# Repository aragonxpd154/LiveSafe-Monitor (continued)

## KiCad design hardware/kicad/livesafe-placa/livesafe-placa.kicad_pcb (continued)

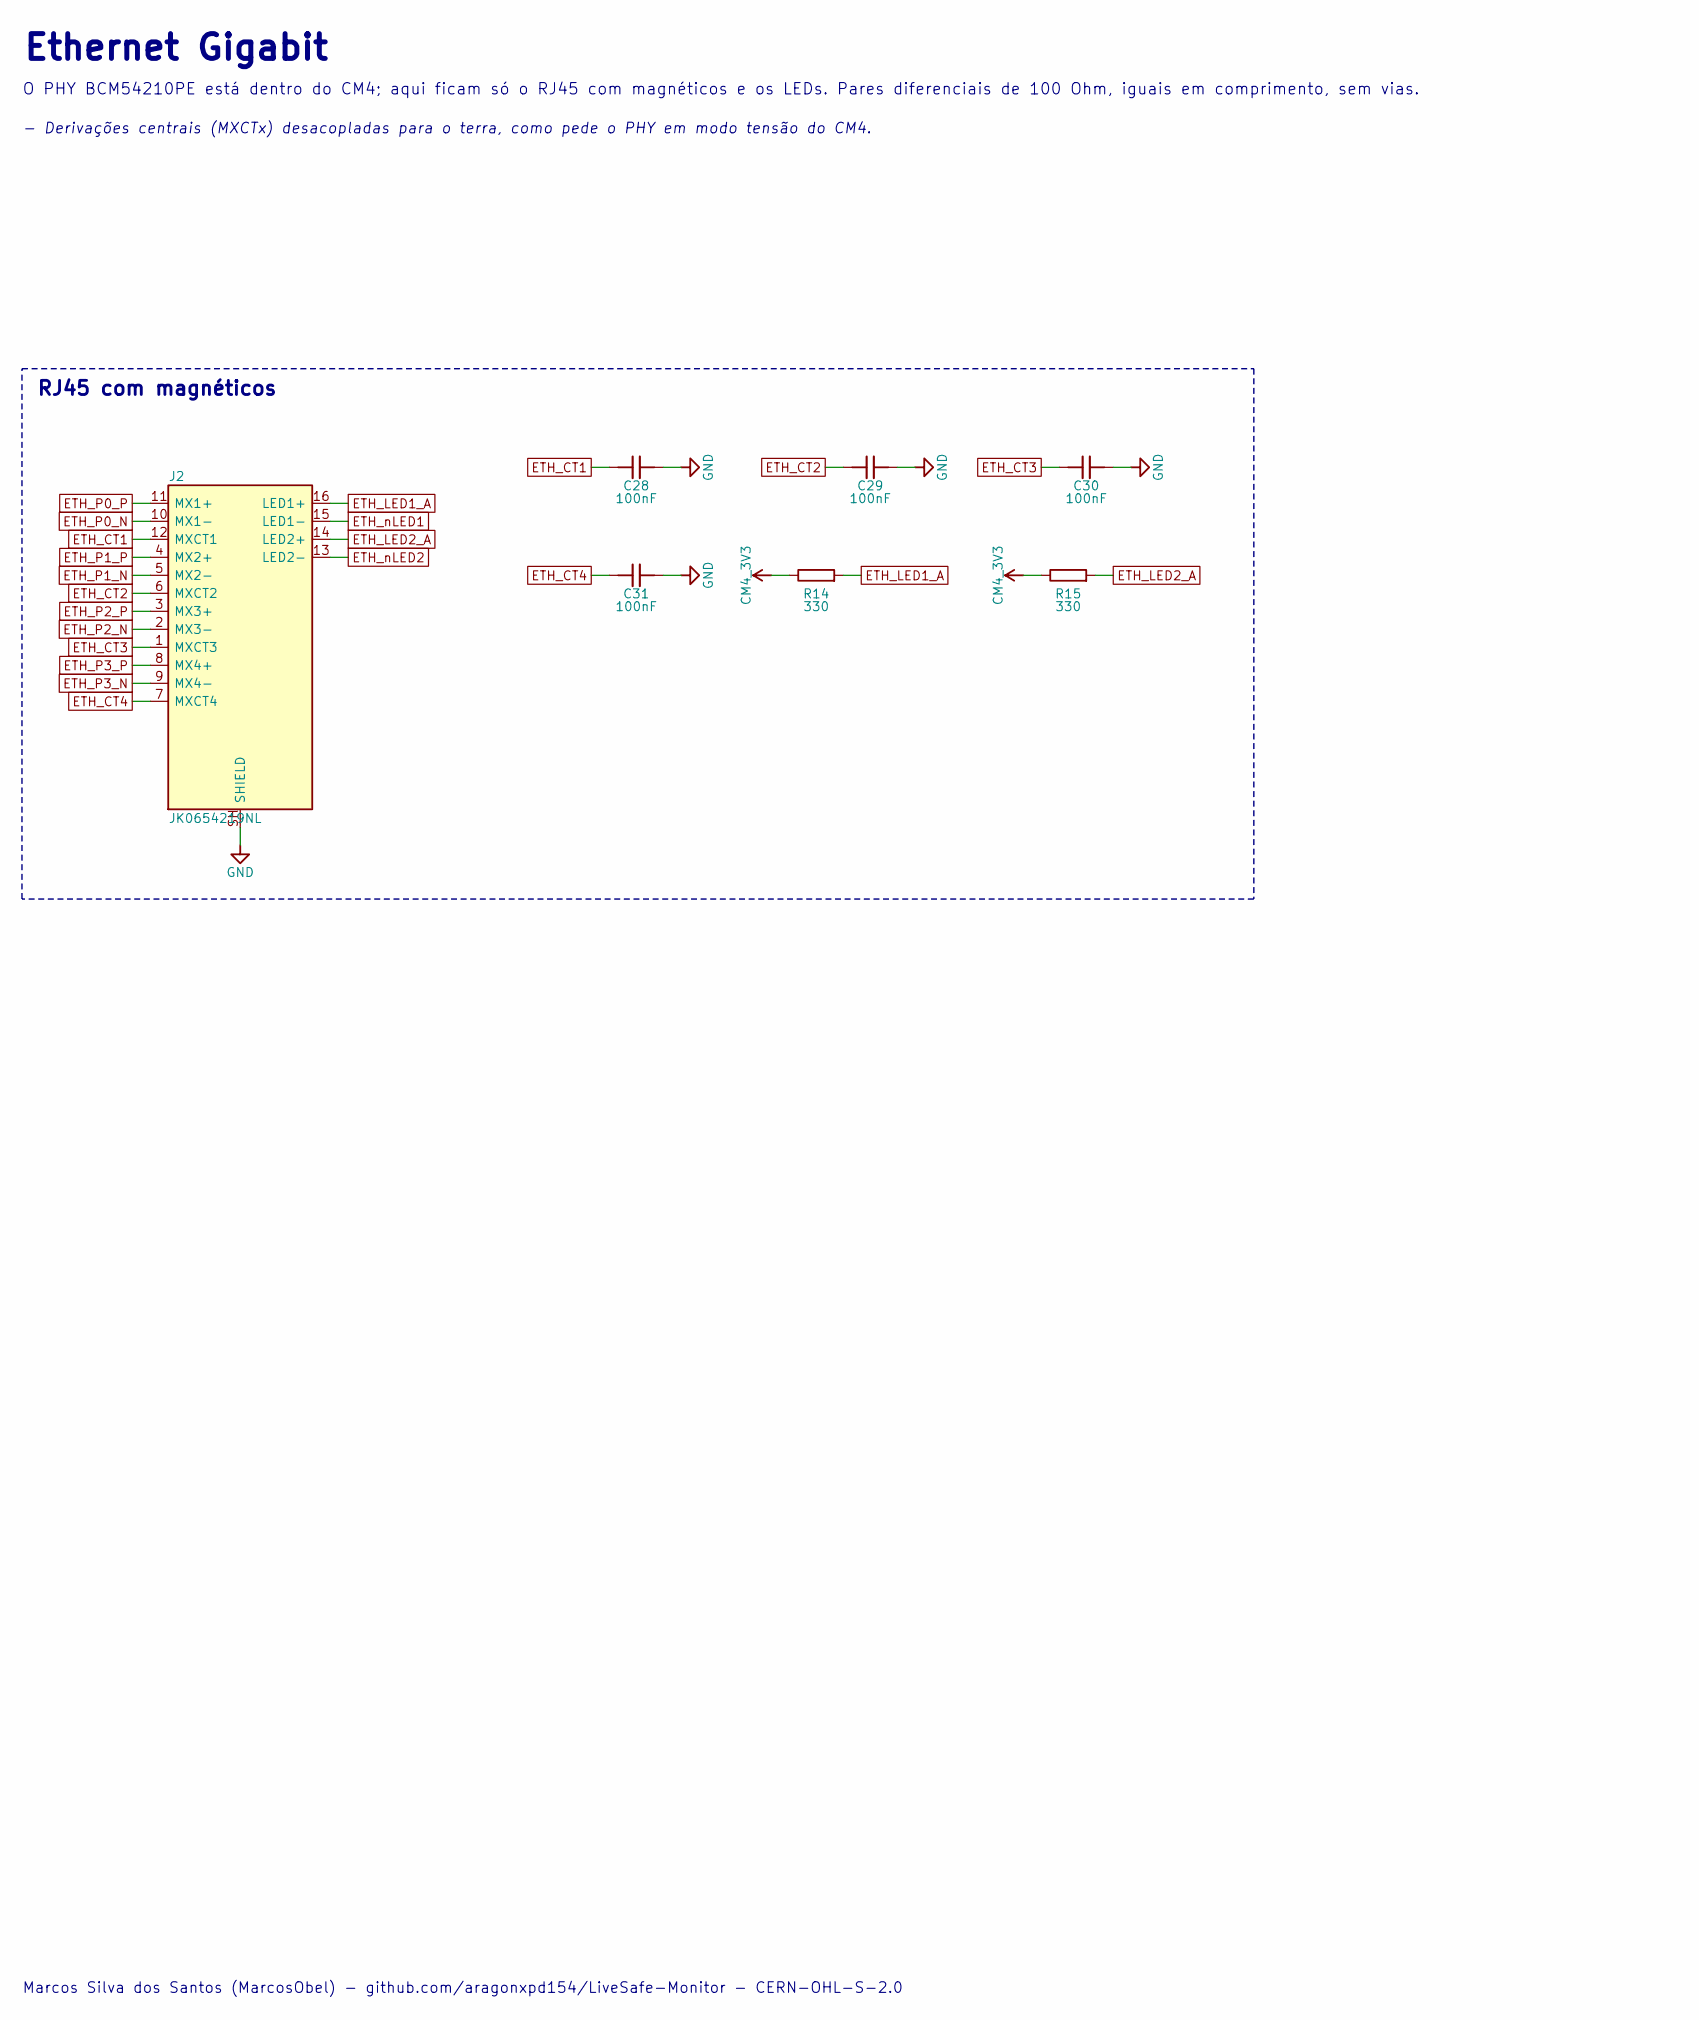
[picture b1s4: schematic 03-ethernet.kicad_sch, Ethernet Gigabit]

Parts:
C28, C29, C30, C31: 100nF; C_0402_1005Metric; MPN CL05B104KO5NNNC; LCSC C1525
J2: JK0654219NL; RJ45_Pulse_JK0654219NL_Horizontal; MPN JK0654219NL
R14, R15: 330; R_0402_1005Metric; MPN 0402WGF3300TCE; LCSC C25104

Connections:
CM4_3V3: R14.1, R15.1; also elsewhere on the board
ETH_CT1: C28.1, J2.12 (MXCT1)
ETH_CT2: C29.1, J2.6 (MXCT2)
ETH_CT3: C30.1, J2.1 (MXCT3)
ETH_CT4: C31.1, J2.7 (MXCT4)
ETH_LED1_A: J2.16 (LED1+), R14.2
ETH_LED2_A: J2.14 (LED2+), R15.2
ETH_P0_N: J2.10 (MX1-); also elsewhere on the board
ETH_P0_P: J2.11 (MX1+); also elsewhere on the board
ETH_P1_N: J2.5 (MX2-); also elsewhere on the board
ETH_P1_P: J2.4 (MX2+); also elsewhere on the board
ETH_P2_N: J2.2 (MX3-); also elsewhere on the board
ETH_P2_P: J2.3 (MX3+); also elsewhere on the board
ETH_P3_N: J2.9 (MX4-); also elsewhere on the board
ETH_P3_P: J2.8 (MX4+); also elsewhere on the board
ETH_nLED1: J2.15 (LED1-); also elsewhere on the board
ETH_nLED2: J2.13 (LED2-); also elsewhere on the board
GND: C28.2, C29.2, C30.2, C31.2, J2.SH (SHIELD); also elsewhere on the board

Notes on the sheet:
RJ45 com magnéticos
Ethernet Gigabit
O PHY BCM54210PE está dentro do CM4; aqui ficam só o RJ45 com magnéticos e os LEDs. Pares diferenciais de 100 Ohm, iguais em comprimento, sem vias.
- Derivações centrais (MXCTx) desacopladas para o terra, como pede o PHY em modo tensão do CM4.
Marcos Silva dos Santos (MarcosObel) - github.com/aragonxpd154/LiveSafe-Monitor - CERN-OHL-S-2.0

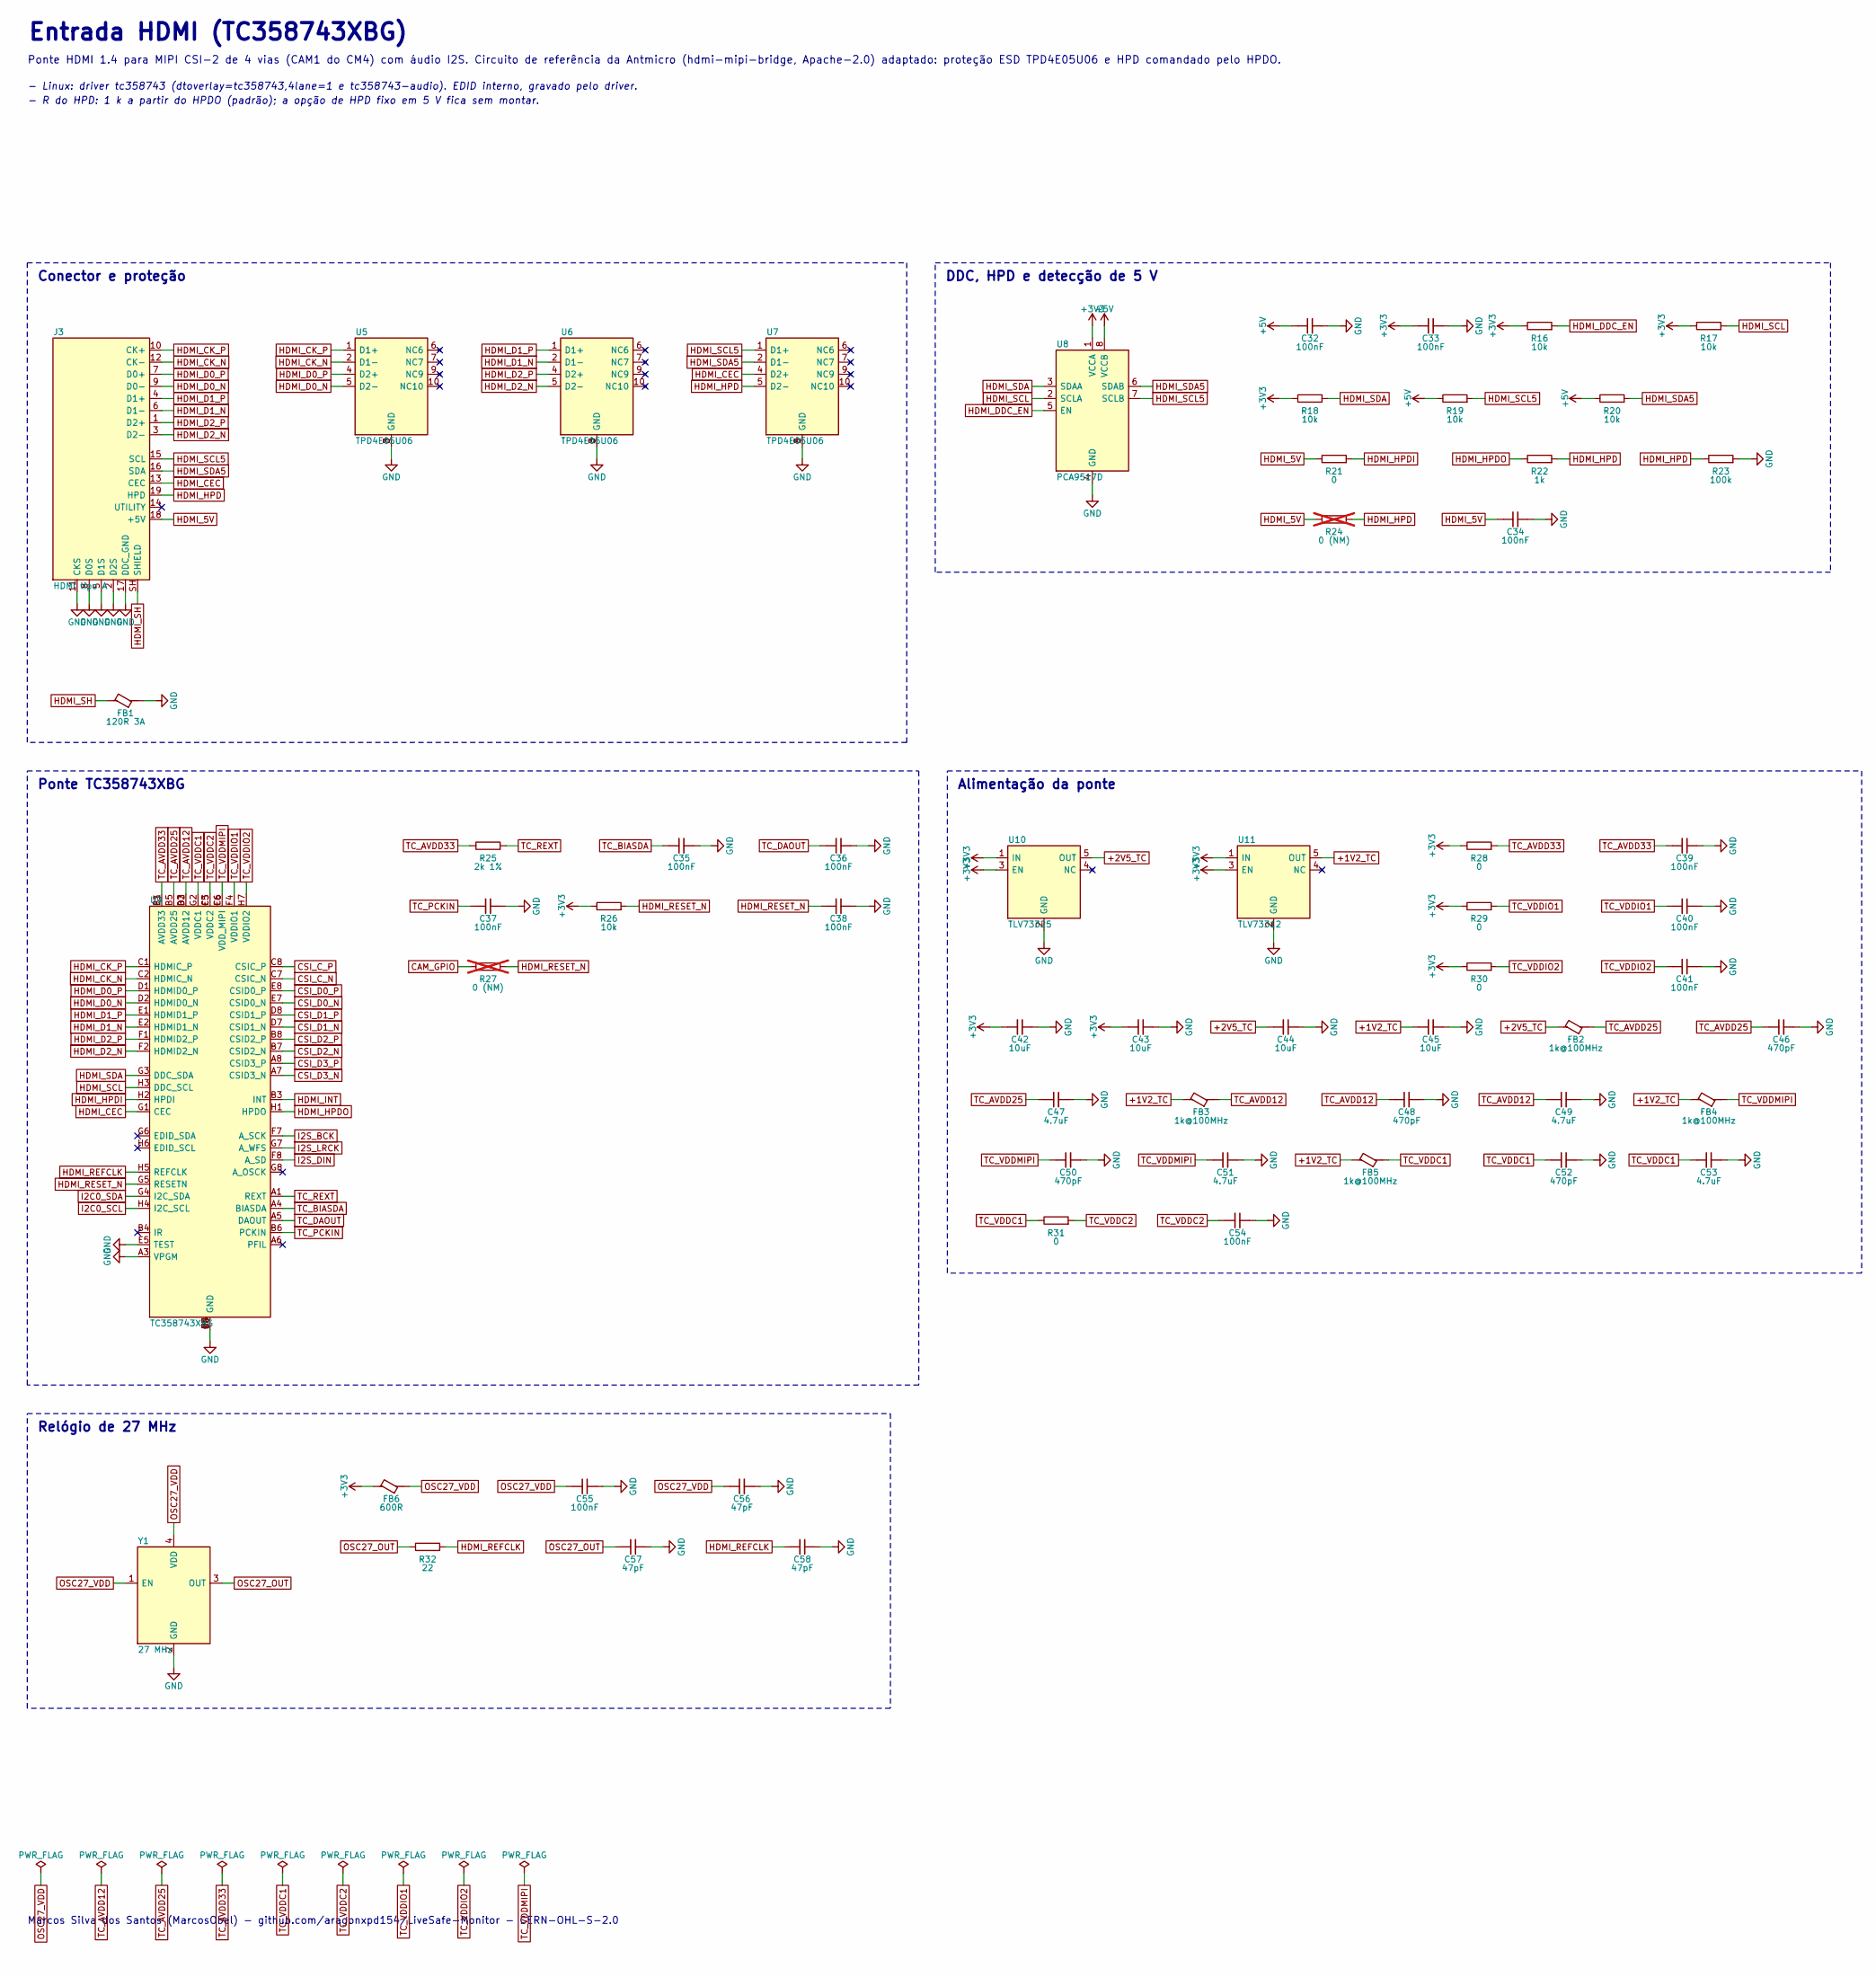
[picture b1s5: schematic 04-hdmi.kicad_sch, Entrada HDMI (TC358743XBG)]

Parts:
C32, C33, C34, C35, C36, C37, C38, C39, C40, C41, C54, C55: 100nF; C_0402_1005Metric; MPN CL05B104KO5NNNC; LCSC C1525
C42, C43, C44, C45: 10uF; C_0603_1608Metric; MPN CL10A106KP8NNNC; LCSC C19702
C46, C48, C50, C52: 470pF; C_0402_1005Metric; MPN CL05B471KB5NNNC; LCSC C26412
C47, C49, C51, C53: 4.7uF; C_0603_1608Metric; MPN CL10A475KO8NNNC; LCSC C19666
C56, C57, C58: 47pF; C_0402_1005Metric; MPN CL05C470JB5NNNC; LCSC C84706
FB1: 120R 3A; L_0603_1608Metric; MPN BLM18SG121TN1D; LCSC C113030
FB2, FB3, FB4, FB5: 1k@100MHz; L_0805_2012Metric; MPN BLM21AG102SN1D; LCSC C85835
FB6: 600R; L_0603_1608Metric; MPN BLM18AG601SN1D; LCSC C19330
J3: HDMI tipo A; HDMI_A_Molex_208658-1001_Horizontal; MPN 2086581001; LCSC C916313
R16, R17, R18, R19, R20, R26: 10k; R_0402_1005Metric; MPN 0402WGF1002TCE; LCSC C25744
R21, R28, R29, R30, R31: 0; R_0603_1608Metric; MPN 0603WAF0000T5E; LCSC C21189
R22: 1k; R_0402_1005Metric; MPN 0402WGF1001TCE; LCSC C11702
R23: 100k; R_0402_1005Metric; MPN 0402WGF1003TCE; LCSC C25741
R24: 0 (NM); R_0603_1608Metric; MPN 0603WAF0000T5E; LCSC C21189; not fitted
R25: 2k 1%; R_0402_1005Metric; MPN 0402WGF2001TCE; LCSC C4109
R27: 0 (NM); R_0402_1005Metric; MPN 0402WGF0000TCE; LCSC C17168; not fitted
R32: 22; R_0402_1005Metric; MPN 0402WGF220JTCE; LCSC C25092
U5, U6, U7: TPD4E05U06; USON-10_2.5x1.0mm_P0.5mm; MPN TPD4E05U06DQAR; LCSC C138714
U8: PCA9517D; SOIC-8_3.9x4.9mm_P1.27mm; MPN PCA9517D,118; LCSC C2652395
U9: TC358743XBG; Toshiba_P-TFBGA64-0606-0.65; MPN TC358743XBG
U10: TLV73325; SOT-23-5; MPN TLV73325PDBVR; LCSC C882825
U11: TLV73312; SOT-23-5; MPN TLV73312PDBVR; LCSC C473364
Y1: 27 MHz; Oscillator_SMD_Abracon_ASE-4Pin_3.2x2.5mm; MPN ASE-27.000MHZ-LC-T; LCSC C1988528

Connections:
+1V2_TC: C45.1, FB3.1, FB4.1, FB5.1, U11.5 (OUT)
+2V5_TC: C44.1, FB2.1, U10.5 (OUT)
+3V3: C33.1, C42.1, C43.1, FB6.1, R16.1, R17.1, R18.1, R26.1, R28.1, R29.1, R30.1, U8.1 (VCCA), U10.1 (IN), U10.3 (EN), U11.1 (IN), U11.3 (EN); also elsewhere on the board
+5V: C32.1, R19.1, R20.1, U8.8 (VCCB); also elsewhere on the board
CAM_GPIO: R27.1; also elsewhere on the board
CSI_C_N: U9.C7 (CSIC_N); also elsewhere on the board
CSI_C_P: U9.C8 (CSIC_P); also elsewhere on the board
CSI_D0_N: U9.E7 (CSID0_N); also elsewhere on the board
CSI_D0_P: U9.E8 (CSID0_P); also elsewhere on the board
CSI_D1_N: U9.D7 (CSID1_N); also elsewhere on the board
CSI_D1_P: U9.D8 (CSID1_P); also elsewhere on the board
CSI_D2_N: U9.B7 (CSID2_N); also elsewhere on the board
CSI_D2_P: U9.B8 (CSID2_P); also elsewhere on the board
CSI_D3_N: U9.A7 (CSID3_N); also elsewhere on the board
CSI_D3_P: U9.A8 (CSID3_P); also elsewhere on the board
GND: C32.2, C33.2, C34.2, C35.2, C36.2, C37.2, C38.2, C39.2, C40.2, C41.2, C42.2, C43.2, C44.2, C45.2, C46.2, C47.2, C48.2, C49.2, C50.2, C51.2, C52.2, C53.2, C54.2, C55.2, C56.2, C57.2, C58.2, FB1.2, J3.2 (D2S), J3.5 (D1S), J3.8 (D0S), J3.11 (CKS), J3.17 (DDC_GND), R23.2, U5.3 (GND), U5.8 (GND), U6.3 (GND), U6.8 (GND), U7.3 (GND), U7.8 (GND), U8.4 (GND), U9.A2 (GND), U9.A3 (VPGM), U9.C4 (GND), U9.C5 (GND), U9.D4 (GND), U9.D5 (GND), U9.D6 (GND), U9.E3 (GND), U9.E4 (GND), U9.E5 (TEST), U9.E6 (GND), U9.H8 (GND), U10.2 (GND), U11.2 (GND), Y1.2 (GND); also elsewhere on the board
HDMI_5V: C34.1, J3.18 (+5V), R21.1, R24.1
HDMI_CEC: J3.13 (CEC), U7.4 (D2+), U9.G1 (CEC)
HDMI_CK_N: J3.12 (CK-), U5.2 (D1-), U9.C2 (HDMIC_N)
HDMI_CK_P: J3.10 (CK+), U5.1 (D1+), U9.C1 (HDMIC_P)
HDMI_D0_N: J3.9 (D0-), U5.5 (D2-), U9.D2 (HDMID0_N)
HDMI_D0_P: J3.7 (D0+), U5.4 (D2+), U9.D1 (HDMID0_P)
HDMI_D1_N: J3.6 (D1-), U6.2 (D1-), U9.E2 (HDMID1_N)
HDMI_D1_P: J3.4 (D1+), U6.1 (D1+), U9.E1 (HDMID1_P)
HDMI_D2_N: J3.3 (D2-), U6.5 (D2-), U9.F2 (HDMID2_N)
HDMI_D2_P: J3.1 (D2+), U6.4 (D2+), U9.F1 (HDMID2_P)
HDMI_DDC_EN: R16.2, U8.5 (EN)
HDMI_HPD: J3.19 (HPD), R22.2, R23.1, R24.2, U7.5 (D2-)
HDMI_HPDI: R21.2, U9.H2 (HPDI)
HDMI_HPDO: R22.1, U9.H1 (HPDO)
HDMI_INT: U9.B3 (INT); also elsewhere on the board
HDMI_REFCLK: C58.1, R32.2, U9.H5 (REFCLK)
HDMI_RESET_N: C38.1, R26.2, R27.2, U9.G5 (RESETN)
HDMI_SCL: R17.2, U8.2 (SCLA), U9.H3 (DDC_SCL)
HDMI_SCL5: J3.15 (SCL), R19.2, U7.1 (D1+), U8.7 (SCLB)
HDMI_SDA: R18.2, U8.3 (SDAA), U9.G3 (DDC_SDA)
HDMI_SDA5: J3.16 (SDA), R20.2, U7.2 (D1-), U8.6 (SDAB)
HDMI_SH: FB1.1, J3.SH (SHIELD)
I2C0_SCL: U9.H4 (I2C_SCL); also elsewhere on the board
I2C0_SDA: U9.G4 (I2C_SDA); also elsewhere on the board
I2S_BCK: U9.F7 (A_SCK); also elsewhere on the board
I2S_DIN: U9.F8 (A_SD); also elsewhere on the board
I2S_LRCK: U9.G7 (A_WFS); also elsewhere on the board
OSC27_OUT: C57.1, R32.1, Y1.3 (OUT)
OSC27_VDD: C55.1, C56.1, FB6.2, Y1.1 (EN), Y1.4 (VDD)
TC_AVDD12: C48.1, C49.1, FB3.2, U9.B2 (AVDD12), U9.D3 (AVDD12)
TC_AVDD25: C46.1, C47.1, FB2.2, U9.B5 (AVDD25)
TC_AVDD33: C39.1, R25.1, R28.2, U9.B1 (AVDD33), U9.F3 (AVDD33)
TC_BIASDA: C35.1, U9.A4 (BIASDA)
TC_DAOUT: C36.1, U9.A5 (DAOUT)
TC_PCKIN: C37.1, U9.B6 (PCKIN)
TC_REXT: R25.2, U9.A1 (REXT)
TC_VDDC1: C52.1, C53.1, FB5.2, R31.1, U9.G2 (VDDC1)
TC_VDDC2: C54.1, R31.2, U9.C3 (VDDC2), U9.F5 (VDDC2)
TC_VDDIO1: C40.1, R29.2, U9.F4 (VDDIO1)
TC_VDDIO2: C41.1, R30.2, U9.H7 (VDDIO2)
TC_VDDMIPI: C50.1, C51.1, FB4.2, U9.C6 (VDD_MIPI), U9.F6 (VDD_MIPI)

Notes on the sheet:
Conector e proteção
DDC, HPD e detecção de 5 V
Ponte TC358743XBG
Alimentação da ponte
Relógio de 27 MHz
Entrada HDMI (TC358743XBG)
Ponte HDMI 1.4 para MIPI CSI-2 de 4 vias (CAM1 do CM4) com áudio I2S. Circuito de referência da Antmicro (hdmi-mipi-bridge, Apache-2.0) adaptado: proteção ESD TPD4E05U06 e HPD comandado pelo HPDO.
- Linux: driver tc358743 (dtoverlay=tc358743,4lane=1 e tc358743-audio). EDID interno, gravado pelo driver.
- R do HPD: 1 k a partir do HPDO (padrão); a opção de HPD fixo em 5 V fica sem montar.
Marcos Silva dos Santos (MarcosObel) - github.com/aragonxpd154/LiveSafe-Monitor - CERN-OHL-S-2.0

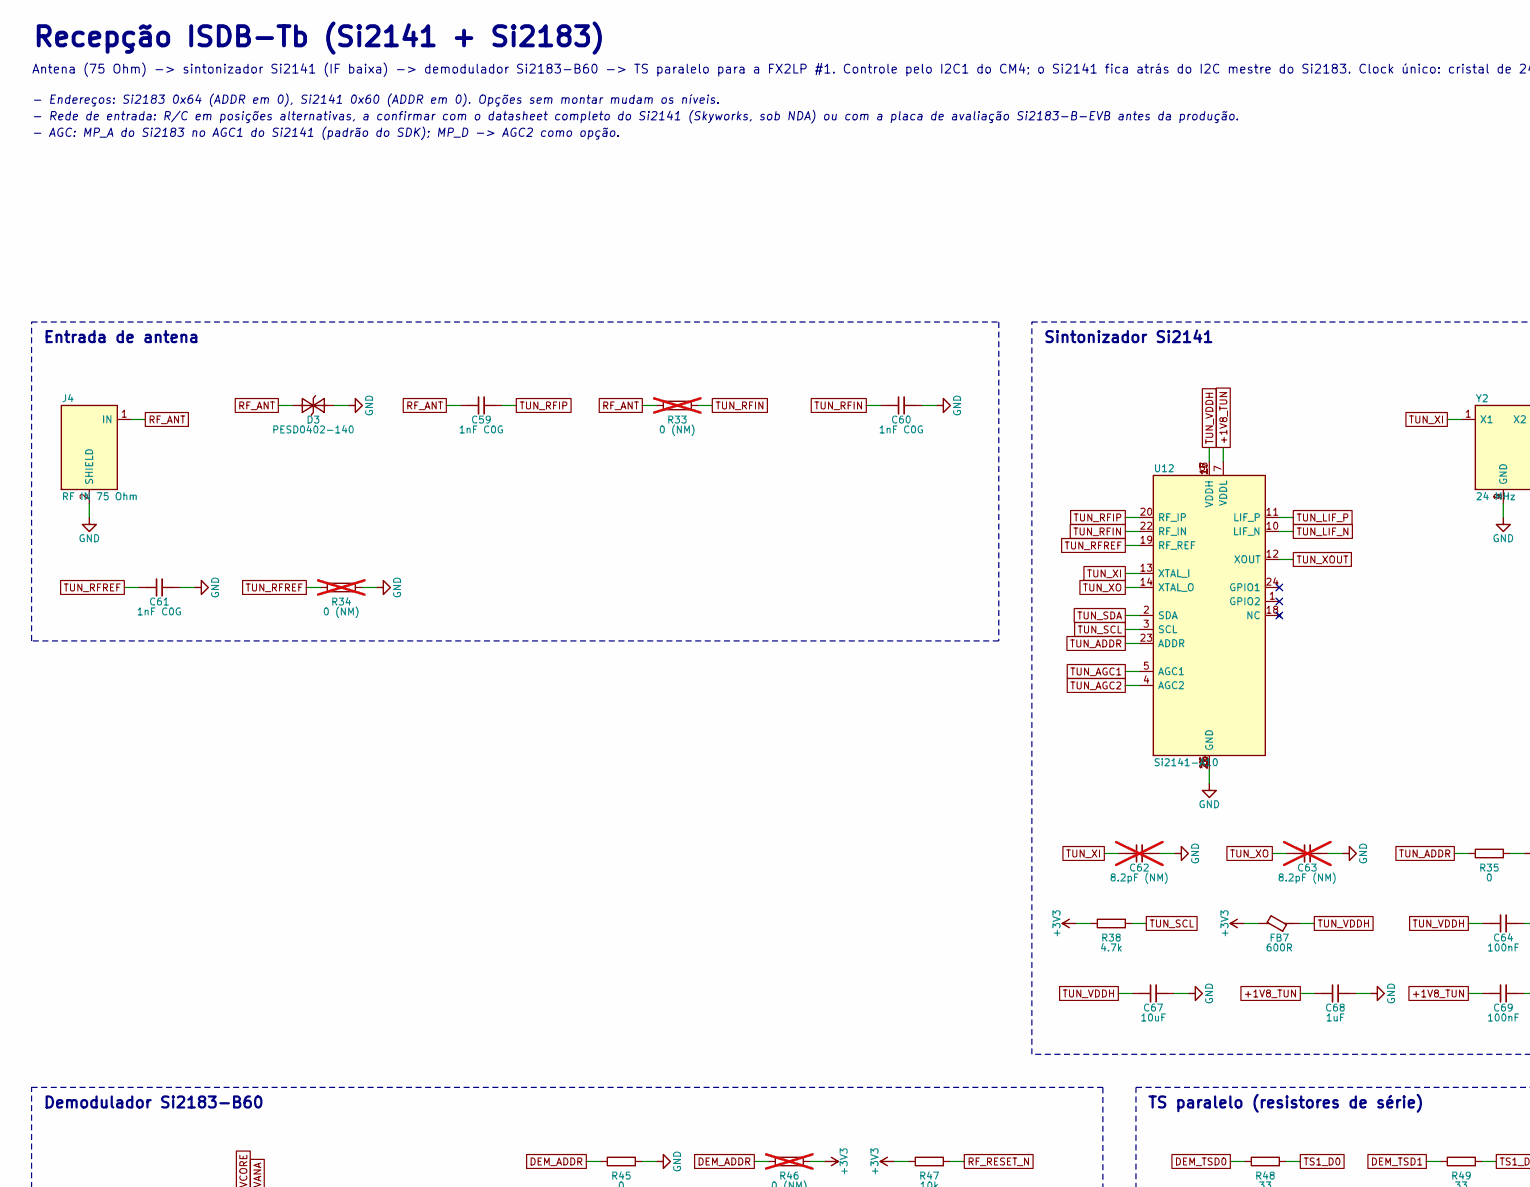
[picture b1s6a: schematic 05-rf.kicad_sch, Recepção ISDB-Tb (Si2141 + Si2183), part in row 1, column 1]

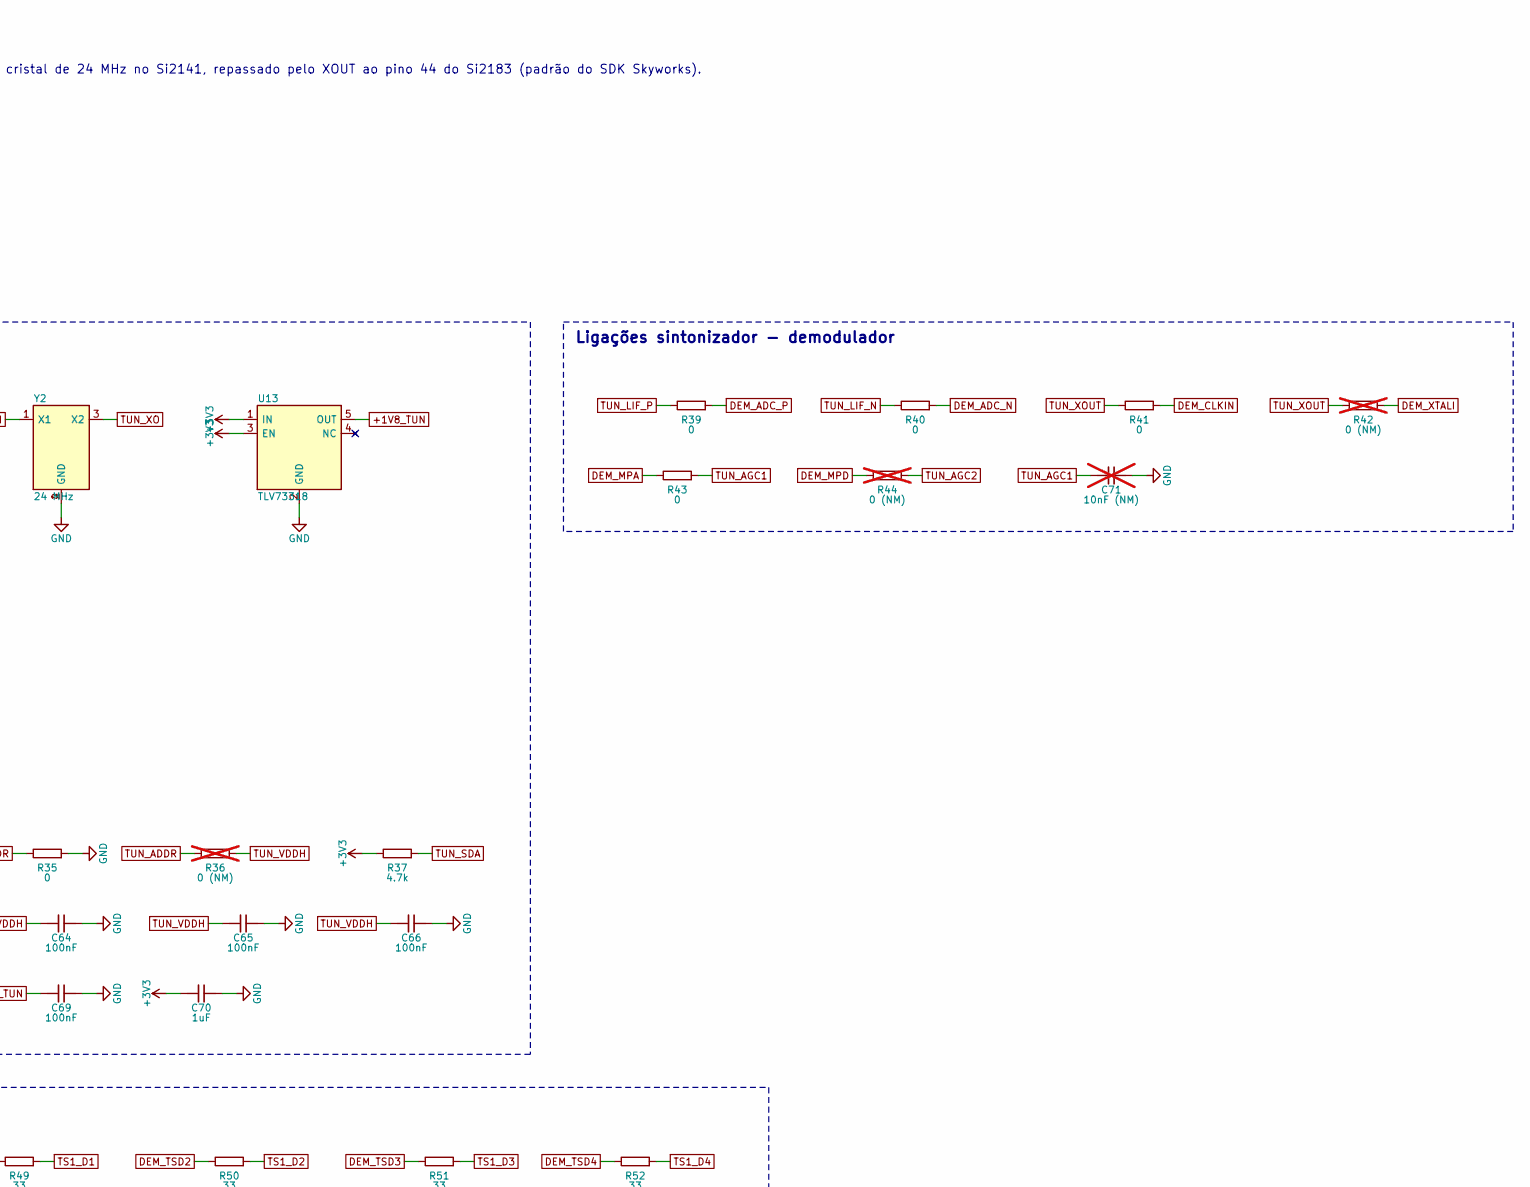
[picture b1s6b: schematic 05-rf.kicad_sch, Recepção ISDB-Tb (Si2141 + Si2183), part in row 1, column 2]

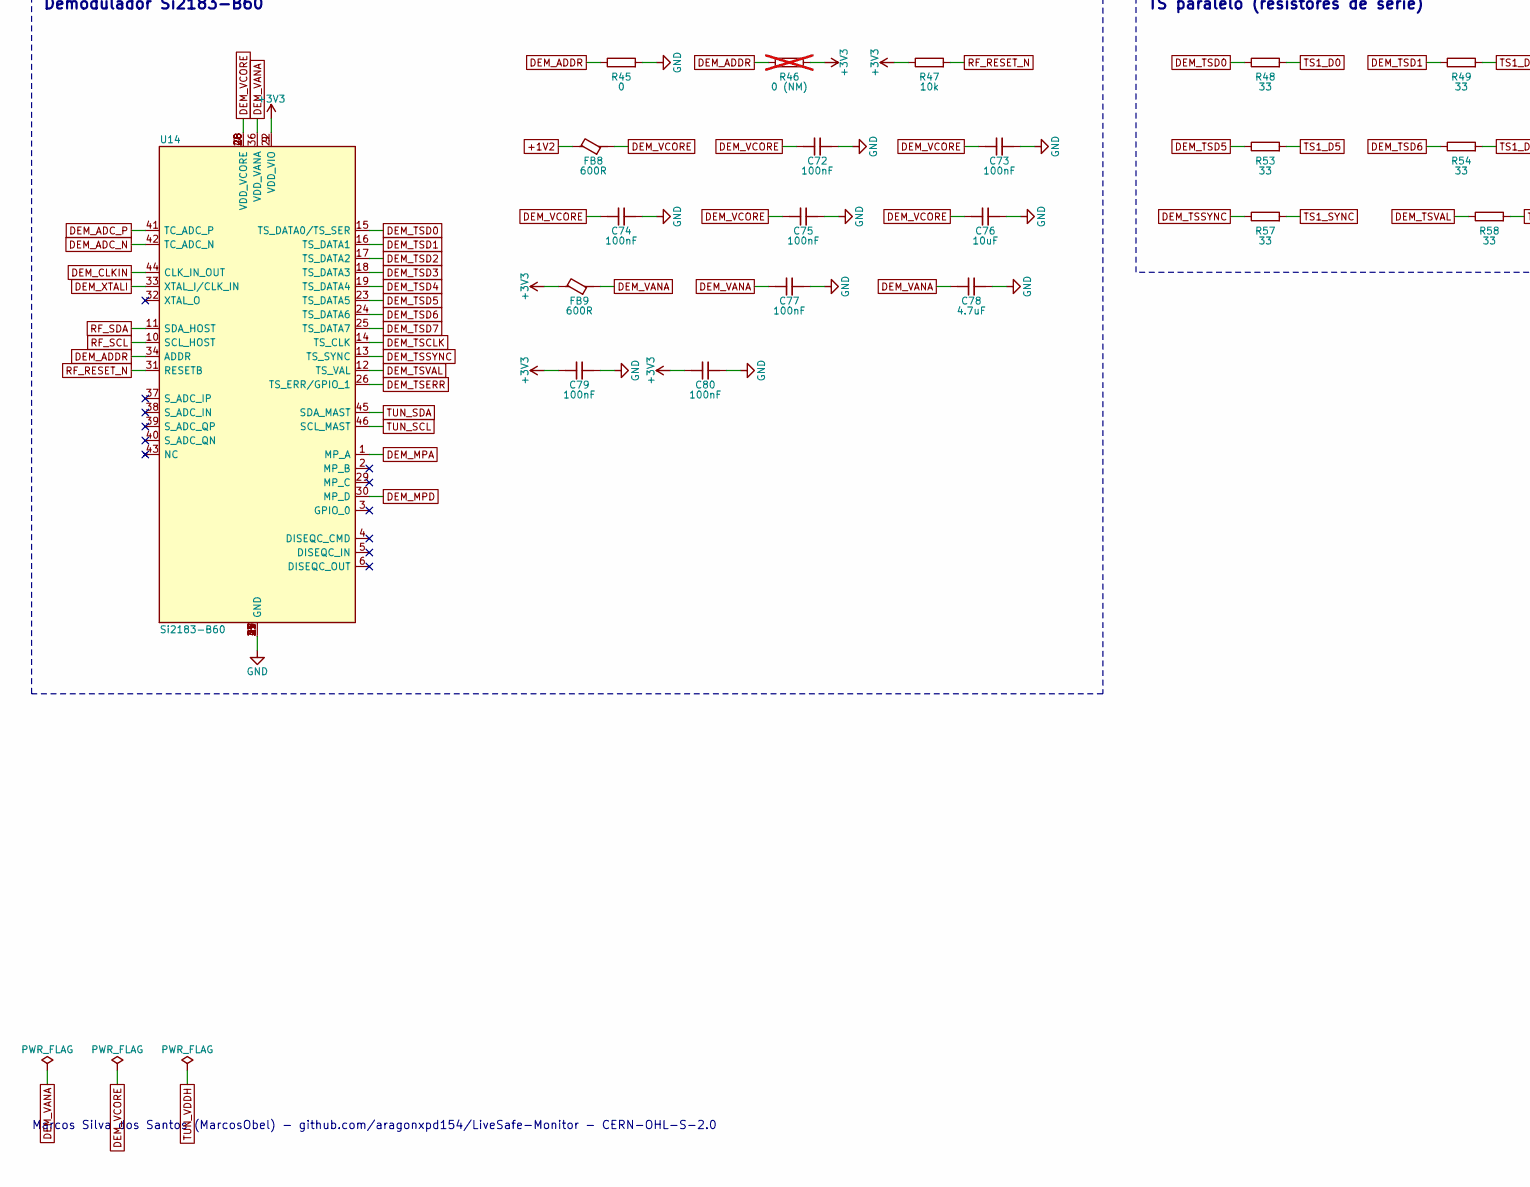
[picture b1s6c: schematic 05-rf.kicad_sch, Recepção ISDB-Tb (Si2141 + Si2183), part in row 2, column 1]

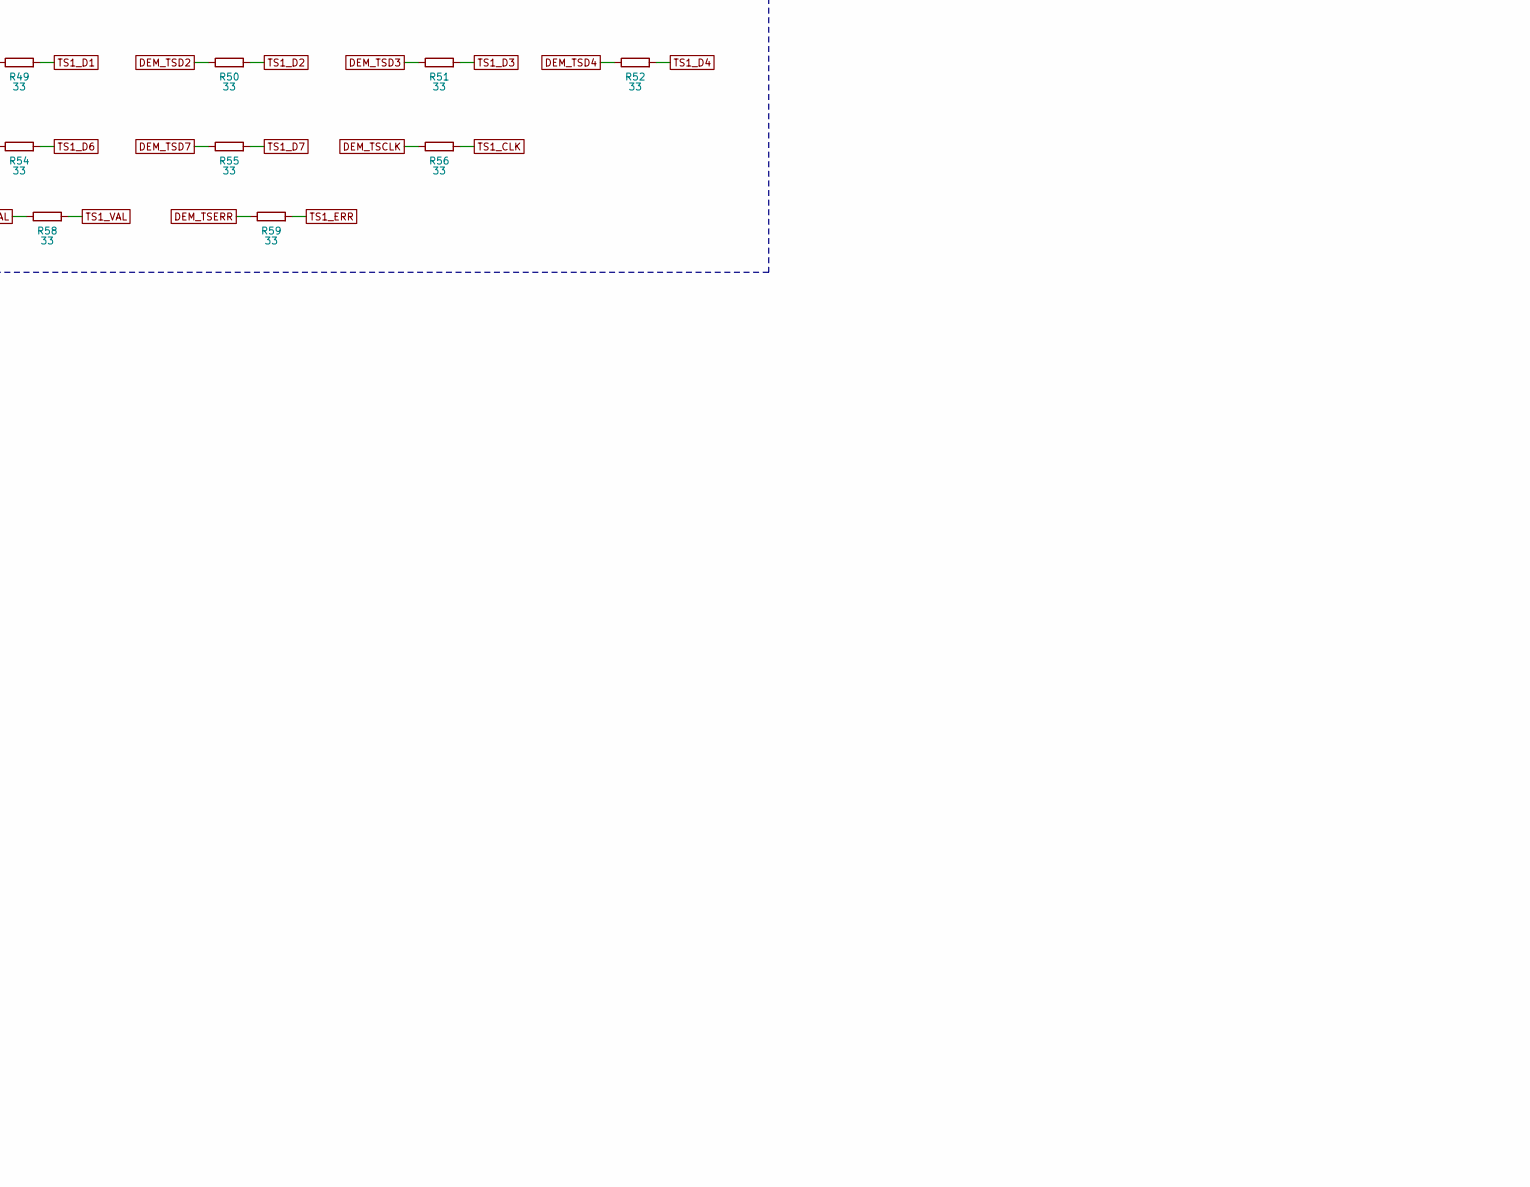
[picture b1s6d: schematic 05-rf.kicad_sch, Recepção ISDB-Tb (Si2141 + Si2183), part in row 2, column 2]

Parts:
C59, C60, C61: 1nF C0G; C_0402_1005Metric; MPN GRM1555C1H102JA01D; LCSC C76947
C62, C63: 8.2pF (NM); C_0402_1005Metric; not fitted
C64, C65, C66, C69, C72, C73, C74, C75, C77, C79, C80: 100nF; C_0402_1005Metric; MPN CL05B104KO5NNNC; LCSC C1525
C67, C76: 10uF; C_0603_1608Metric; MPN CL10A106KP8NNNC; LCSC C19702
C68, C70: 1uF; C_0402_1005Metric; MPN CL05A105KA5NQNC; LCSC C52923
C71: 10nF (NM); C_0402_1005Metric; not fitted
C78: 4.7uF; C_0603_1608Metric; MPN CL10A475KO8NNNC; LCSC C19666
D3: PESD0402-140; D_0402_1005Metric; MPN PESD0402-140; LCSC C10662
FB7, FB8, FB9: 600R; L_0603_1608Metric; MPN BLM18AG601SN1D; LCSC C19330
J4: RF IN 75 Ohm; BNC_Amphenol_B6252HB-NPP3G-50_Horizontal; MPN B6252HB-NPP3G-75
R33, R34, R36, R42, R44, R46: 0 (NM); R_0402_1005Metric; MPN 0402WGF0000TCE; LCSC C17168; not fitted
R35, R39, R40, R41, R43, R45: 0; R_0402_1005Metric; MPN 0402WGF0000TCE; LCSC C17168
R37, R38: 4.7k; R_0402_1005Metric; MPN 0402WGF4701TCE; LCSC C25900
R47: 10k; R_0402_1005Metric; MPN 0402WGF1002TCE; LCSC C25744
R48, R49, R50, R51, R52, R53, R54, R55, R56, R57, R58, R59: 33; R_0402_1005Metric; MPN 0402WGF330JTCE; LCSC C25105
U12: Si2141-A10; Skyworks_QFN-24_3x3mm_P0.4mm_EP1.7mm_CornerPads; MPN Si2141-A10-GM; LCSC C430209
U13: TLV73318; SOT-23-5; MPN TLV73318PDBVR; LCSC C882824
U14: Si2183-B60; QFN-48-1EP_7x7mm_P0.5mm_EP5.15x5.15mm; MPN Si2183-B60-GM; LCSC C2654249
Y2: 24 MHz; Crystal_SMD_3225-4Pin_3.2x2.5mm; MPN X322524MOB4SI; LCSC C70590

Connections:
+1V2: FB8.1; also elsewhere on the board
+1V8_TUN: C68.1, C69.1, U12.7 (VDDL), U13.5 (OUT)
+3V3: C70.1, C79.1, C80.1, FB7.1, FB9.1, R37.1, R38.1, R46.2, R47.1, U13.1 (IN), U13.3 (EN), U14.9 (VDD_VIO), U14.22 (VDD_VIO); also elsewhere on the board
DEM_ADC_N: R40.2, U14.42 (TC_ADC_N)
DEM_ADC_P: R39.2, U14.41 (TC_ADC_P)
DEM_ADDR: R45.1, R46.1, U14.34 (ADDR)
DEM_CLKIN: R41.2, U14.44 (CLK_IN_OUT)
DEM_MPA: R43.1, U14.1 (MP_A)
DEM_MPD: R44.1, U14.30 (MP_D)
DEM_TSCLK: R56.1, U14.14 (TS_CLK)
DEM_TSD0: R48.1, U14.15 (TS_DATA0/TS_SER)
DEM_TSD1: R49.1, U14.16 (TS_DATA1)
DEM_TSD2: R50.1, U14.17 (TS_DATA2)
DEM_TSD3: R51.1, U14.18 (TS_DATA3)
DEM_TSD4: R52.1, U14.19 (TS_DATA4)
DEM_TSD5: R53.1, U14.23 (TS_DATA5)
DEM_TSD6: R54.1, U14.24 (TS_DATA6)
DEM_TSD7: R55.1, U14.25 (TS_DATA7)
DEM_TSERR: R59.1, U14.26 (TS_ERR/GPIO_1)
DEM_TSSYNC: R57.1, U14.13 (TS_SYNC)
DEM_TSVAL: R58.1, U14.12 (TS_VAL)
DEM_VANA: C77.1, C78.1, FB9.2, U14.36 (VDD_VANA)
DEM_VCORE: C72.1, C73.1, C74.1, C75.1, C76.1, FB8.2, U14.7 (VDD_VCORE), U14.20 (VDD_VCORE), U14.28 (VDD_VCORE), U14.48 (VDD_VCORE)
DEM_XTALI: R42.2, U14.33 (XTAL_I/CLK_IN)
GND: C60.2, C61.2, C62.2, C63.2, C64.2, C65.2, C66.2, C67.2, C68.2, C69.2, C70.2, C71.2, C72.2, C73.2, C74.2, C75.2, C76.2, C77.2, C78.2, C79.2, C80.2, D3.2 (A), J4.2 (SHIELD), R34.2, R35.2, R45.2, U12.6 (GND), U12.8 (GND), U12.16 (GND), U12.21 (GND), U12.25 (GND), U13.2 (GND), U14.8 (GND), U14.21 (GND), U14.27 (GND), U14.35 (GND), U14.47 (GND), U14.49 (GND), Y2.2 (GND), Y2.4 (GND); also elsewhere on the board
RF_ANT: C59.1, D3.1 (K), J4.1 (IN), R33.1
RF_RESET_N: R47.2, U14.31 (RESETB); also elsewhere on the board
RF_SCL: U14.10 (SCL_HOST); also elsewhere on the board
RF_SDA: U14.11 (SDA_HOST); also elsewhere on the board
TS1_CLK: R56.2; also elsewhere on the board
TS1_D0: R48.2; also elsewhere on the board
TS1_D1: R49.2; also elsewhere on the board
TS1_D2: R50.2; also elsewhere on the board
TS1_D3: R51.2; also elsewhere on the board
TS1_D4: R52.2; also elsewhere on the board
TS1_D5: R53.2; also elsewhere on the board
TS1_D6: R54.2; also elsewhere on the board
TS1_D7: R55.2; also elsewhere on the board
TS1_ERR: R59.2; also elsewhere on the board
TS1_SYNC: R57.2; also elsewhere on the board
TS1_VAL: R58.2; also elsewhere on the board
TUN_ADDR: R35.1, R36.1, U12.23 (ADDR)
TUN_AGC1: C71.1, R43.2, U12.5 (AGC1)
TUN_AGC2: R44.2, U12.4 (AGC2)
TUN_LIF_N: R40.1, U12.10 (LIF_N)
TUN_LIF_P: R39.1, U12.11 (LIF_P)
TUN_RFIN: C60.1, R33.2, U12.22 (RF_IN)
TUN_RFIP: C59.2, U12.20 (RF_IP)
TUN_RFREF: C61.1, R34.1, U12.19 (RF_REF)
TUN_SCL: R38.2, U12.3 (SCL), U14.46 (SCL_MAST)
TUN_SDA: R37.2, U12.2 (SDA), U14.45 (SDA_MAST)
TUN_VDDH: C64.1, C65.1, C66.1, C67.1, FB7.2, R36.2, U12.9 (VDDH), U12.15 (VDDH), U12.17 (VDDH)
TUN_XI: C62.1, U12.13 (XTAL_I), Y2.1 (X1)
TUN_XO: C63.1, U12.14 (XTAL_O), Y2.3 (X2)
TUN_XOUT: R41.1, R42.1, U12.12 (XOUT)

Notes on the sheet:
Entrada de antena
Sintonizador Si2141
Ligações sintonizador - demodulador
Demodulador Si2183-B60
TS paralelo (resistores de série)
Recepção ISDB-Tb (Si2141 + Si2183)
Antena (75 Ohm) -> sintonizador Si2141 (IF baixa) -> demodulador Si2183-B60 -> TS paralelo para a FX2LP #1. Controle pelo I2C1 do CM4; o Si2141 fica atrás do I2C mestre do Si2183. Clock único: cristal de 24 MHz no Si2141, repassado pelo XOUT ao pino 44 do Si2183 (padrão do SDK Skyworks).
- Endereços: Si2183 0x64 (ADDR em 0), Si2141 0x60 (ADDR em 0). Opções sem montar mudam os níveis.
- Rede de entrada: R/C em posições alternativas, a confirmar com o datasheet completo do Si2141 (Skyworks, sob NDA) ou com a placa de avaliação Si2183-B-EVB antes da produção.
- AGC: MP_A do Si2183 no AGC1 do Si2141 (padrão do SDK); MP_D -> AGC2 como opção.
Marcos Silva dos Santos (MarcosObel) - github.com/aragonxpd154/LiveSafe-Monitor - CERN-OHL-S-2.0
